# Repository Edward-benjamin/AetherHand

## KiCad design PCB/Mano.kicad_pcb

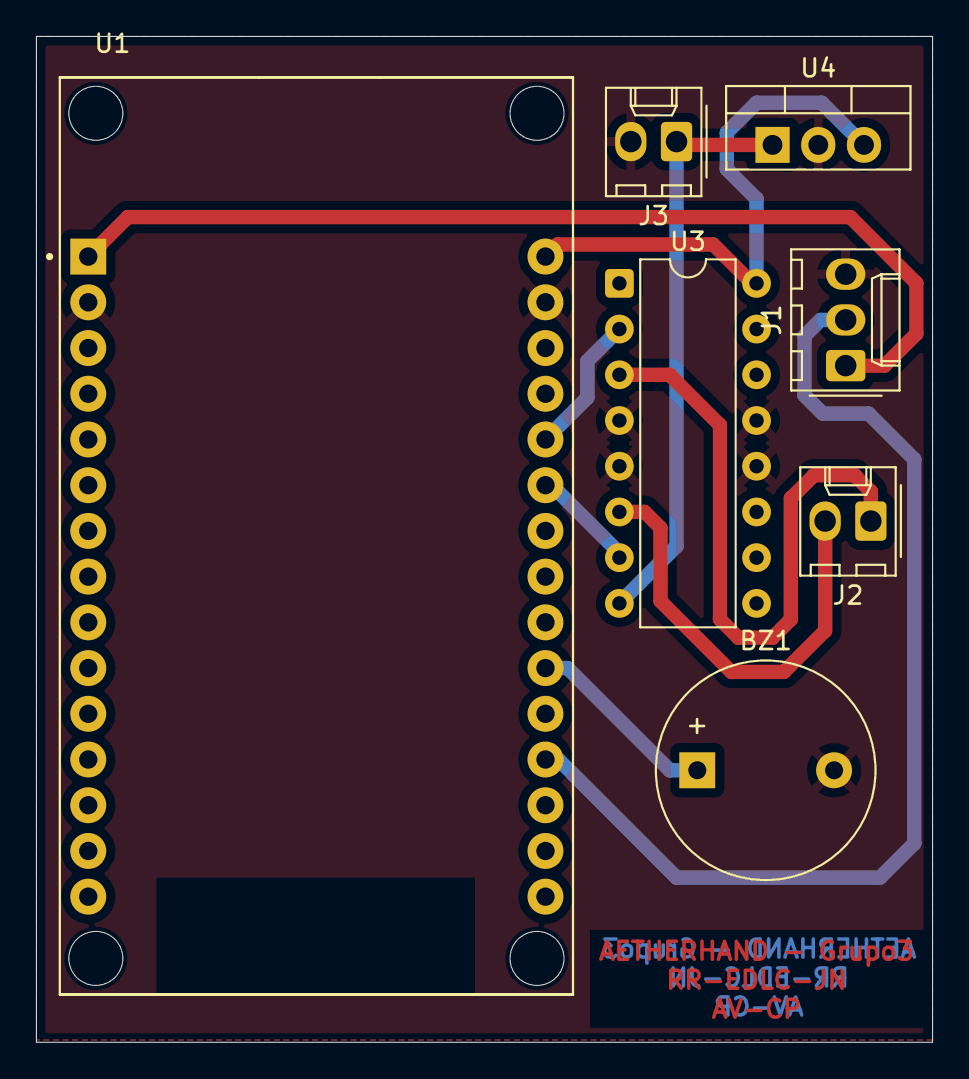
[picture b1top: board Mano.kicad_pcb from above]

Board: 2 copper layers, 49.8 x 55.9 mm, 7 parts (0 on the bottom side), 10 nets.

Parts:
BZ1: Buzzer; Buzzer_12x9.5RM7.6
J1: Sensores; Molex_KK-254_AE-6410-03A_1x03_P2.54mm_Vertical
J2: Mano; Molex_KK-254_AE-6410-02A_1x02_P2.54mm_Vertical
J3: ALI; Molex_KK-254_AE-6410-02A_1x02_P2.54mm_Vertical
U1: ESP32-DEVKIT-V1; MODULE_ESP32_DEVKIT_V1
U3: L293D; DIP-16_W7.62mm
U4: L7805CV; TO-220-3_Vertical

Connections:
+12V: J3.1, U3.8 (VCC2), U4.1 (IN)
/Mano/3.3V: J1.1, U1.1 (3V3)
/Mano/5V/5V: U1.30 (VIN), U3.16 (VCC1), U4.3 (OUT)
/Mano/BUZZER/GPIO 32: BZ1.1 (+), U1.21 (D32)
/Mano/Controlador de motor/GPIO 14: U1.26 (D14), U3.2 (1A)
/Mano/Controlador de motor/GPIO 27: U1.25 (D27), U3.7 (2A)
/Mano/D34: J1.2, U1.19 (D34)
/Mano/MOTOR A: J2.1, U3.3 (1Y)
/Mano/MOTOR B: J2.2, U3.6 (2Y)
GND: BZ1.2 (-), J1.3, J3.2, U1.2 (GND), U1.29 (GND), U3.4 (GND), U3.5 (GND), U3.12 (GND), U3.13 (GND), U4.2

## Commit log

2025-12-07 Create Hola
2025-12-07 Create Holapcb
2025-12-07 Create hola mundo
